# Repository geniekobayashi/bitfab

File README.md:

bitfab
======
These electonics gadgets are going to be available at eMAKERshop. http://www.emakershop.com/Seller=928

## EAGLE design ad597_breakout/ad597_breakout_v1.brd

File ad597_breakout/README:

AD597 thermocouple amp breakout board for RepRap 3D printer.

Inspired by Ultimaker Thermocouple Sensor Board, and made with the same footprint.
http://wiki.ultimaker.com/Thermocouple_Sensor_Board_v2

Cad Data: EAGLE version 6.4

Material: FR4 1oz 2layers 1.6mm

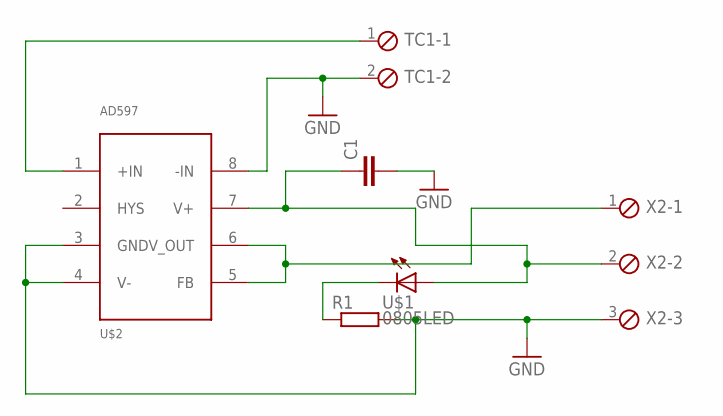
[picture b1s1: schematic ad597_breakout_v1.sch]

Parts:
C1: C-EUC0805; C0805
R1: R-EU_R0805; R0805
TC1: MPT2; 2POL254
U$1: 0805LED
U$2: AD597; SOP8
X2: MPT3; 3POL254

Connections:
GND: C1.2, R1.2, TC1.2, U$2.3 (GND), U$2.4 (V-), U$2.8 (-IN), X2.3
unnamed: TC1.1, U$2.1 (+IN)
unnamed: R1.1, U$1.C
unnamed: U$2.5 (FB), U$2.6 (V_OUT), X2.1
VCC: C1.1, U$1.A, U$2.7 (V+), X2.2

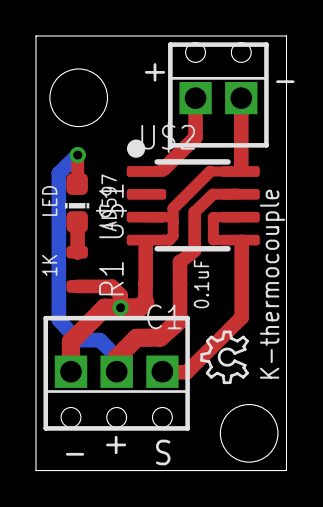
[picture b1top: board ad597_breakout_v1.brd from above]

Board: 2 copper layers, 13.9 x 24.1 mm, 7 parts (0 on the bottom side), 5 nets.

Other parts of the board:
LOGO1: OSHW_LOGO_6MILX0100-NT; OSHW_6X100_NOTEXT

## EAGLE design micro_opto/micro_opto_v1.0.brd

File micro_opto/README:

Optical endstop switch design for RepRap 3D printer.

Cad Data: EAGLE version 6.4
V1.0 - Original
V1.1 - Black resist with original design
V1.2 - Almost mirrored design of original (for Rostock)

Material: FR4 1oz 2layers 1.6mm

* It is no longer made as Toshiba TLP841 photointerrupter is discontinued product.

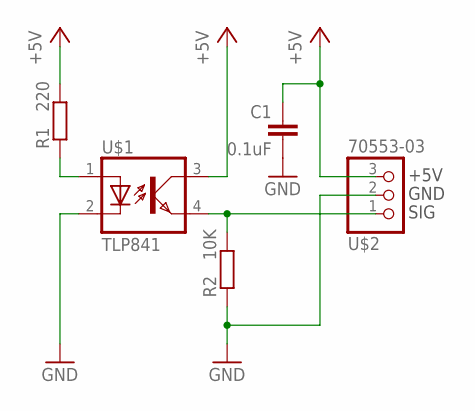
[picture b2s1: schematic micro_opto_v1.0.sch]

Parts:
C1: 0.1uF; C0805
R1: 220; R0805
R2: 10K; R0805
U$1: TLP841
U$2: 70553-03

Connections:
+5V: C1.1, R1.2, U$1.3 (COL), U$2.3
GND: C1.2, R2.1, U$1.2 (C), U$2.2
unnamed: R1.1, U$1.1 (A)
SIG: R2.2, U$1.4 (EMIT), U$2.1

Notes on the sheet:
+5V
GND
SIG

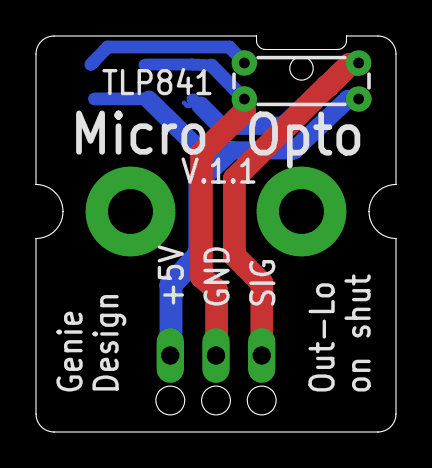
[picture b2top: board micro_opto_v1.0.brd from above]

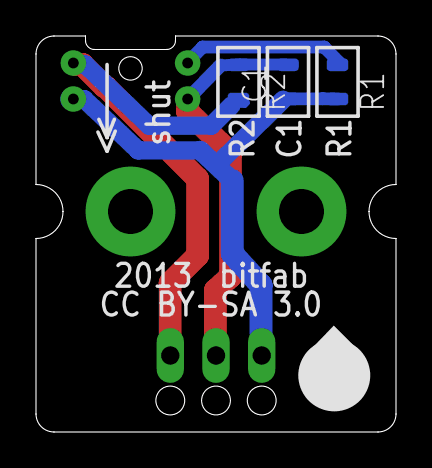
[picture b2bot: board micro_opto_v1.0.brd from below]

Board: 2 copper layers, 20.0 x 22.0 mm, 5 parts (3 on the bottom side), 4 nets.

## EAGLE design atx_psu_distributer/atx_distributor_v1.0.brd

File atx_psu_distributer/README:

ATX power distributer design for RepRap 3D printer.

Referenced to ATX12V Power Supply Design Guide.
http://www.formfactors.org/developer/specs/ATX12V%20PSDG2.01.pdf

Inspired by UltiMachine ATX PSU Dev Board.
https://ultimachine.com/content/atx-psu-dev-board

Cad Data: EAGLE version 6.4
V1.0 - Dual DC12V output
V2.0 - Triple DC12V output

Material: FR4 1oz 2layers 1.6mm

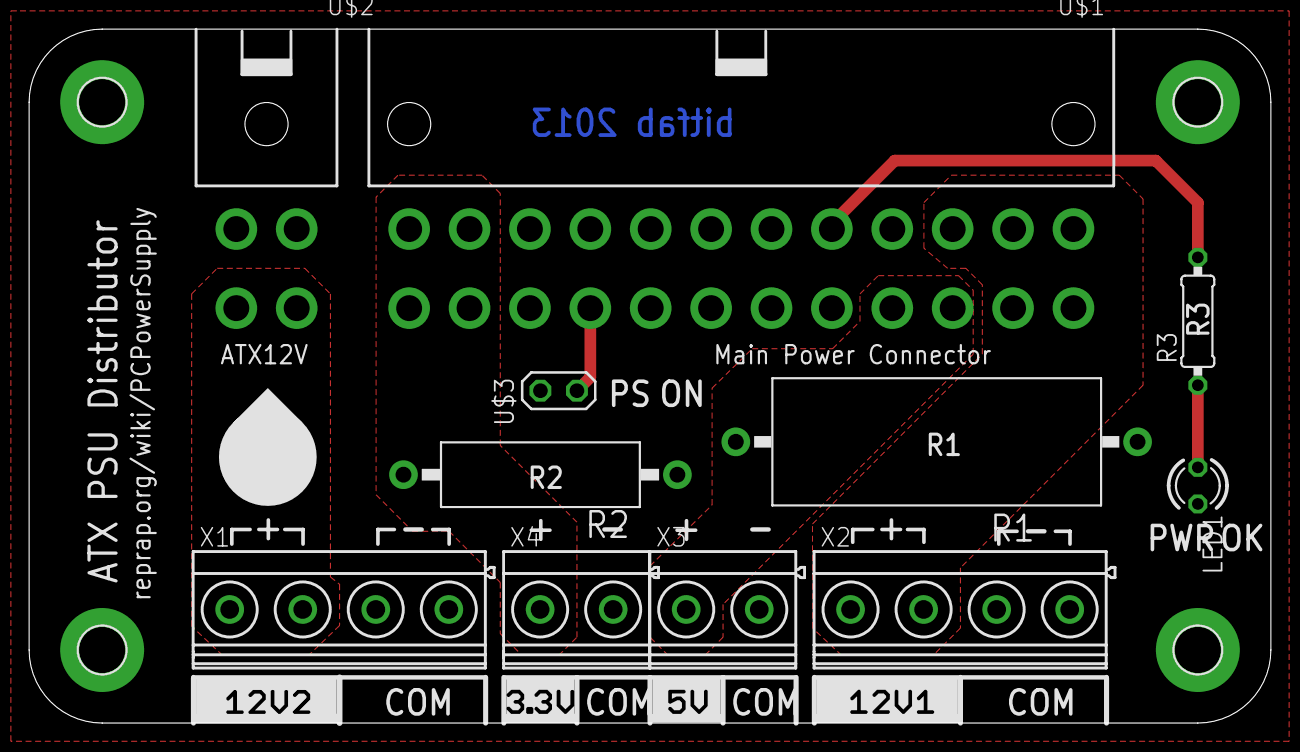
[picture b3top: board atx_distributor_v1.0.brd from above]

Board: 2 copper layers, 86.4 x 48.3 mm, 15 parts (0 on the bottom side), 8 nets.

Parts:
H1, H2, H3, H4: MOUNT-PAD-ROUND3.2; 3,2-PAD
LED1: LED3MM
R1: 20R/5W; HPS923
R2: 220R/3W; CA4050
R3: 1K; 0207/10
U$1: ATX24-REVERSIBLE; ATX24
U$2: ATX2X2
U$3: PINHD-2X1
X1, X2: MKDSN1,5/4-5,08
X3, X4: MKDSN1,5/2-5,08

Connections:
12V2: U$2.3, U$2.4, X1.1, X1.2
+3V3: R2.2, U$1.1, U$1.2, U$1.13, X4.1
+5V: R1.2, U$1.21, U$1.22, U$1.23, X3.1
+12V: U$1.10, U$1.11, X2.1, X2.2
GND: H1.B3,2, H2.B3,2, H3.B3,2, H4.B3,2, LED1.K, R1.1, R2.1, U$1.3, U$1.5, U$1.7, U$1.15, U$1.17, U$1.18, U$1.19, U$2.1, U$2.2, U$3.2, X1.3, X1.4, X2.3, X2.4, X3.2, X4.2
unnamed: U$1.16, U$3.1
unnamed: LED1.A, R3.1
PWR_OK: R3.2, U$1.8

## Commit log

2014-03-25 Electronic gadgets for RepRap
2014-03-25 Renamed
2014-03-27 Edited
2015-04-13 CC BY-NC 3.0

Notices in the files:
atx_psu_distributer/atx_distributor_v1.0.brd:
Creative Commons
micro_opto/micro_opto_v1.0.brd:
CC BY-SA 3.0
parts and their libraries:
SparkFun: Licensing: CC v3.0 Share-Alike You are welcome to use this library for commercial purposes.
